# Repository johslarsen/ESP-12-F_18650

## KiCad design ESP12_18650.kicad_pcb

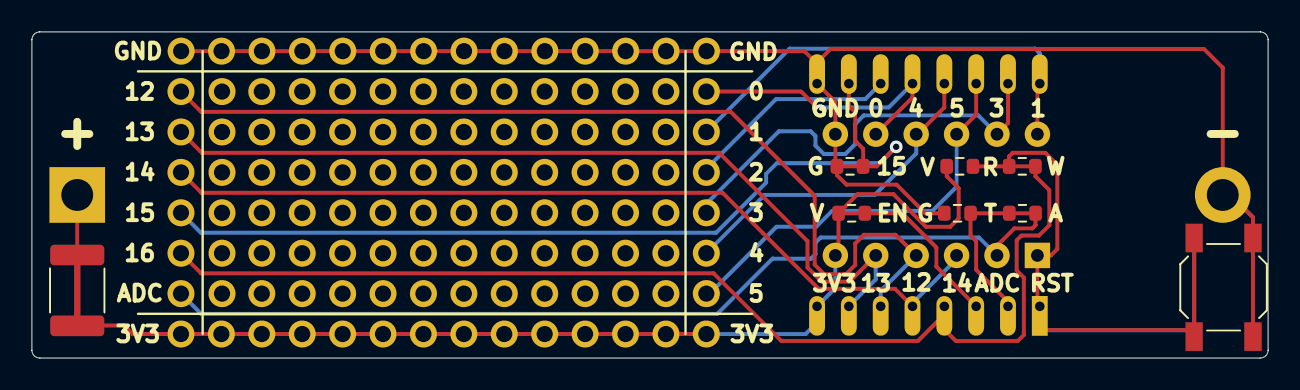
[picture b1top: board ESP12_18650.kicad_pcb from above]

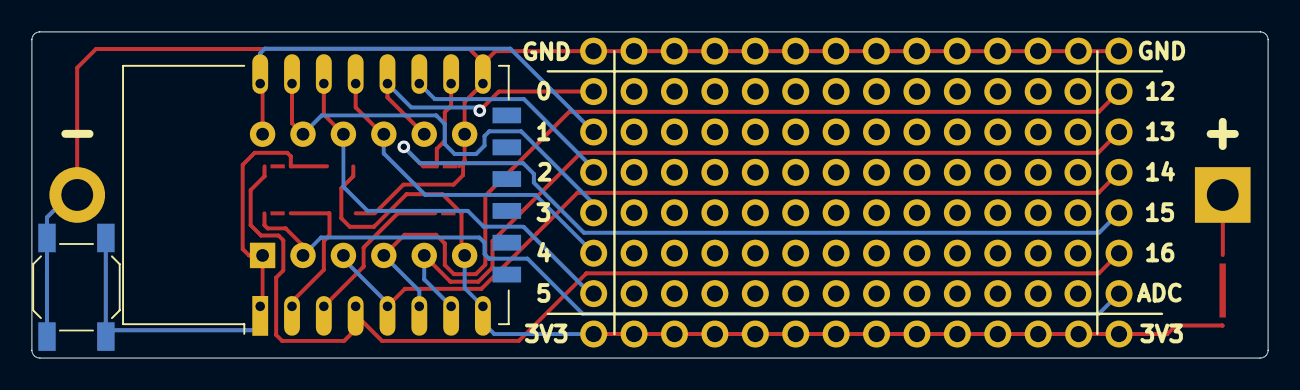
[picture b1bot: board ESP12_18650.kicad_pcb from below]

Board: 2 copper layers, 77.7 x 20.5 mm, 28 parts (3 on the bottom side), 18 nets.

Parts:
BT1: Battery_Cell; BatteryHolder_MPD_BH-18650-PC2
F1: 0R; Fuse_1812_4532Metric_Pad1.30x3.40mm_HandSolder
J1: Conn_02x06_Counter_Clockwise; DIP-12_W7.62mm
J2, J17: Conn_01x14_Male; Standalone_1x14
J3, J4, J5, J6, J7, J8, J9, J10, J11, J12, J13, J14, J15, J16: Conn_01x06_Male; Standalone_1x06
R1, R2, R4, R5: 0R; R_0603_1608Metric_Bridged
R3: 10K; R_0603_1608Metric
R6: OPEN; R_0603_1608Metric
SW1, SW2: SW_Push; SW_SPST_SKQG_WithStem
U1: ESP-12F; ESP-12E_THT

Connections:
/ADC: J1.2, J3.6, R5.1
/EN: R1.2, U1.3 (EN)
/IO0: J1.8, J16.6, U1.18 (GPIO0)
/IO1: J1.12, J16.5, U1.22 (GPIO1/TXD)
/IO2: J16.4, U1.17 (GPIO2)
/IO3: J1.11, J16.3, U1.21 (GPIO3/RXD)
/IO4: J1.9, J16.2, U1.19 (GPIO4)
/IO5: J1.10, J16.1, U1.20 (GPIO5)
/IO12: J1.4, J3.1, U1.6 (GPIO12)
/IO13: J1.5, J3.2, U1.7 (GPIO13)
/IO14: J1.3, J3.3, U1.5 (GPIO14)
/IO15: J3.4, R2.2, U1.16 (GPIO15)
/IO16: J3.5, R4.2, U1.4 (GPIO16)
/RST: J1.1, R3.2, R4.1, SW1.1, SW2.1, U1.1 (~RST)
/TOUT: R5.2, R6.1, U1.2 (ADC)
GND: BT1.2 (-), J1.7, J17.1, J17.2, J17.3, J17.4, J17.5, J17.6, J17.7, J17.8, J17.9, J17.10, J17.11, J17.12, J17.13, J17.14, R2.1, R6.2, SW1.2, SW2.2, U1.15 (GND)
unnamed: BT1.1 (+), F1.1
VCC: F1.2, J1.6, J2.1, J2.2, J2.3, J2.4, J2.5, J2.6, J2.7, J2.8, J2.9, J2.10, J2.11, J2.12, J2.13, J2.14, R1.1, R3.1, U1.8 (VCC)

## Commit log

2022-08-30 Add some footprint libraries
2022-08-30 Finish the initial version of the PCB
2022-08-30 Add +/- battery pole labels
2022-08-30 Flip battery holder (looks better in 3D), and fix/avoid CRC errors
2022-09-03 Add 0.5mm rounding on the edges
2022-09-30 Move dimensions to F.Fab
2022-09-30 Export ESP12_18650_v1.0.zip gerbers
2022-10-05 Fix netname and silkscreen for GPIO 0
2022-10-05 Move IO0 to right side, and ADC to left
2022-10-06 Reorganize connection to eliminate vias
2022-10-06 Export ESP12_18650_v1.1.zip gerbers
